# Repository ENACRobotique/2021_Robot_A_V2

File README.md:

# 2021_Robot_A_V2
Code source robot 2A 2021

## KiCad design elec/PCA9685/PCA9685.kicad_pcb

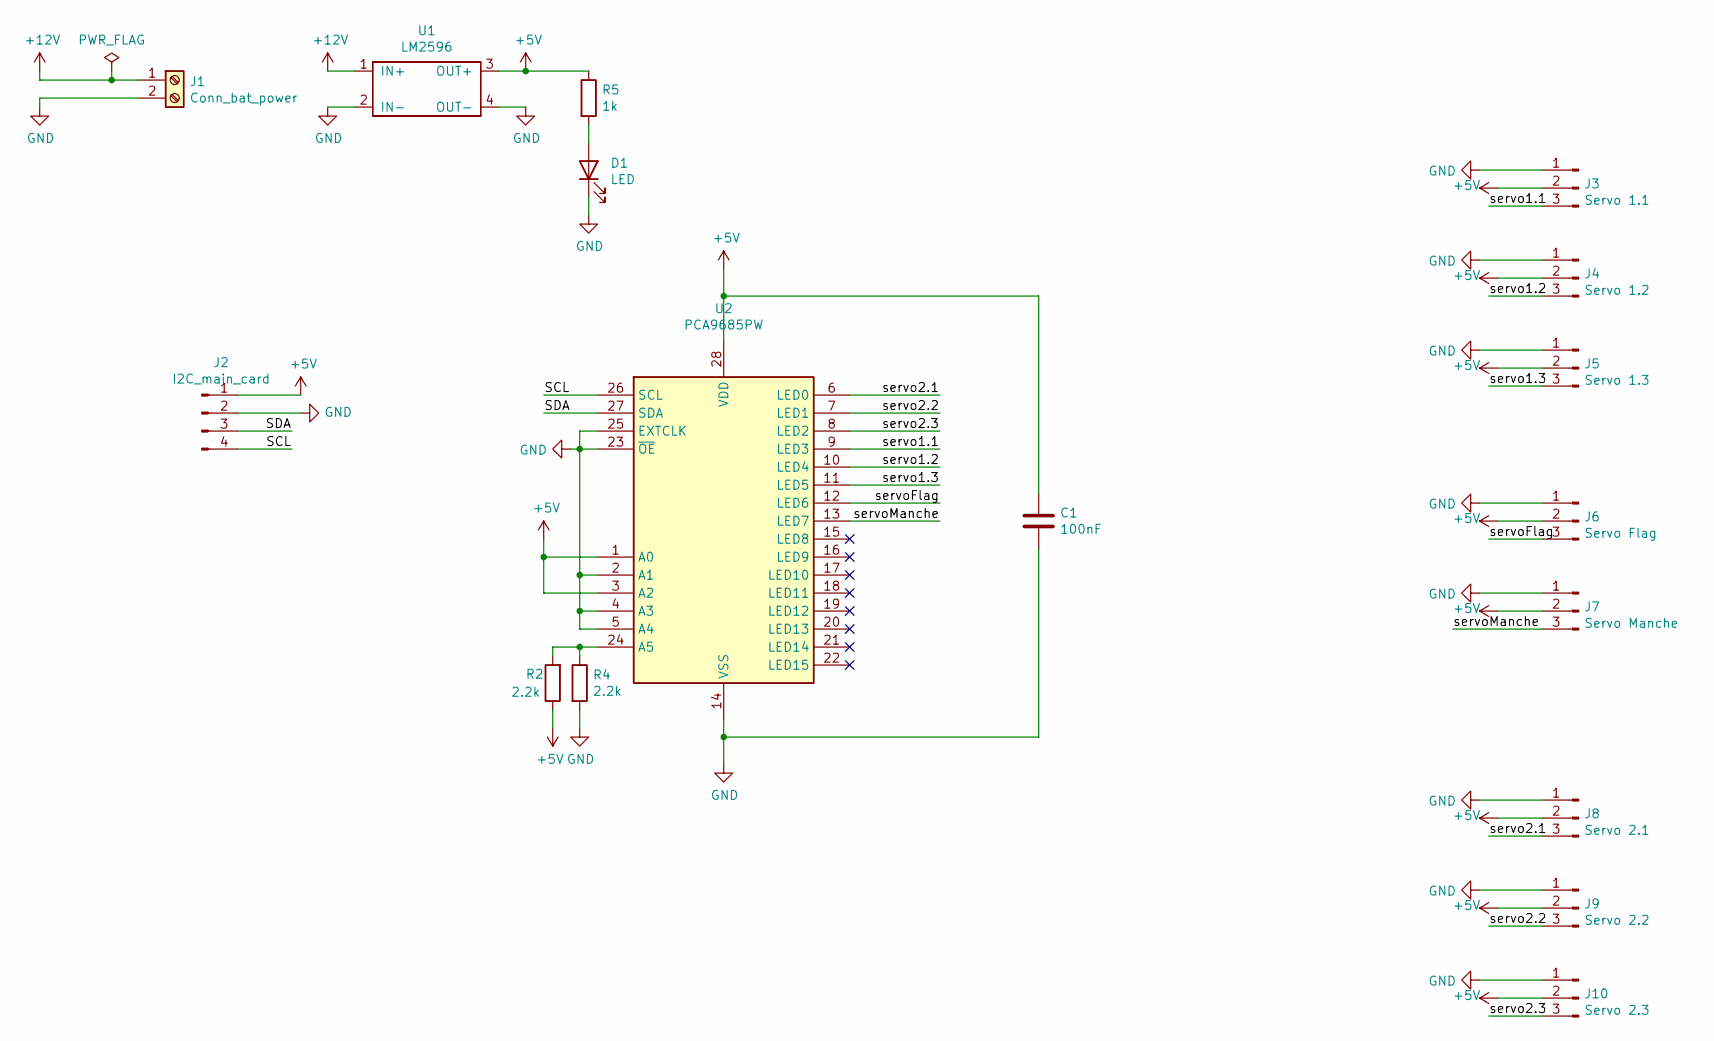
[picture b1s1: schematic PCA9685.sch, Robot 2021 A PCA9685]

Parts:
C1: 100nF; C_0805_2012Metric_Pad1.15x1.40mm_HandSolder
D1: LED; LED_0603_1608Metric_Pad1.05x0.95mm_HandSolder
J1: Conn_bat_power; TerminalBlock_bornier-2_P5.08mm
J2: I2C_main_card; JST_XH_B4B-XH-A_1x04_P2.50mm_Vertical
J3: Servo 1.1; PinHeader_1x03_P2.54mm_Vertical
J4: Servo 1.2; PinHeader_1x03_P2.54mm_Vertical
J5: Servo 1.3; PinHeader_1x03_P2.54mm_Vertical
J6: Servo Flag; PinHeader_1x03_P2.54mm_Vertical
J7: Servo Manche; PinHeader_1x03_P2.54mm_Vertical
J8: Servo 2.1; PinHeader_1x03_P2.54mm_Vertical
J9: Servo 2.2; PinHeader_1x03_P2.54mm_Vertical
J10: Servo 2.3; PinHeader_1x03_P2.54mm_Vertical
R2, R4: 2.2k; R_0805_2012Metric_Pad1.15x1.40mm_HandSolder
R5: 1k; R_0805_2012Metric_Pad1.15x1.40mm_HandSolder
U1: LM2596
U2: PCA9685PW; TSSOP-28_4.4x9.7mm_P0.65mm

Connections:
+5V: C1.1, J2.1, J3.2, J4.2, J5.2, J6.2, J7.2, J8.2, J9.2, J10.2, R2.1, R5.1, U1.3 (OUT+), U2.1 (A0), U2.3 (A2), U2.28 (VDD)
+12V: J1.1, U1.1 (IN+)
/SCL: J2.4, U2.26 (SCL)
/SDA: J2.3, U2.27 (SDA)
/servo1.1: J3.3, U2.9 (LED3)
/servo1.2: J4.3, U2.10 (LED4)
/servo1.3: J5.3, U2.11 (LED5)
/servo2.1: J8.3, U2.6 (LED0)
/servo2.2: J9.3, U2.7 (LED1)
/servo2.3: J10.3, U2.8 (LED2)
/servoFlag: J6.3, U2.12 (LED6)
/servoManche: J7.3, U2.13 (LED7)
GND: C1.2, D1.1 (K), J1.2, J2.2, J3.1, J4.1, J5.1, J6.1, J7.1, J8.1, J9.1, J10.1, R4.2, U1.2 (IN-), U1.4 (OUT-), U2.2 (A1), U2.4 (A3), U2.5 (A4), U2.14 (VSS), U2.23 (~OE), U2.25 (EXTCLK)
unnamed: D1.2 (A), R5.2
unnamed: R2.2, R4.1, U2.24 (A5)

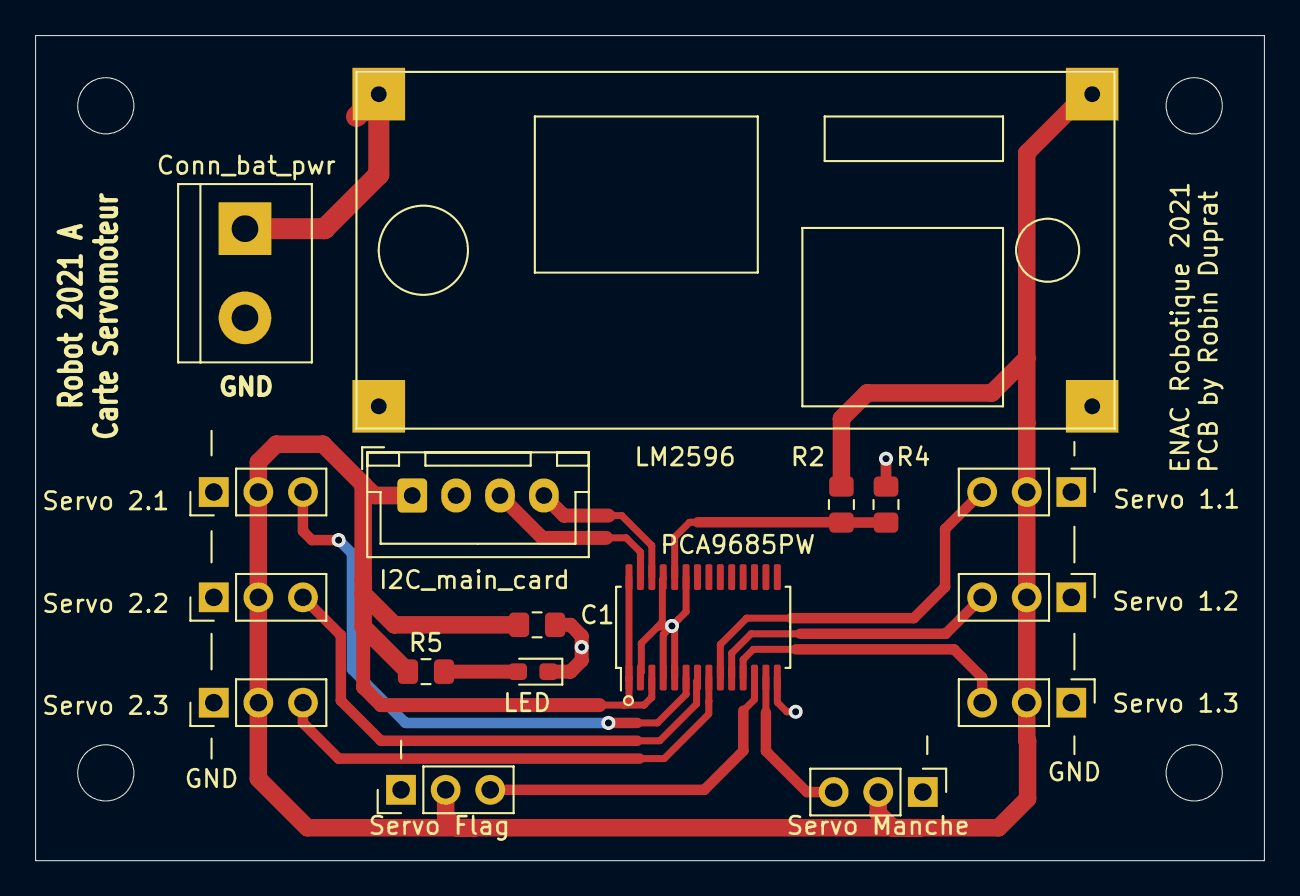
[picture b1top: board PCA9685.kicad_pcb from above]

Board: 2 copper layers, 70.0 x 47.0 mm, 17 parts (0 on the bottom side), 15 nets.

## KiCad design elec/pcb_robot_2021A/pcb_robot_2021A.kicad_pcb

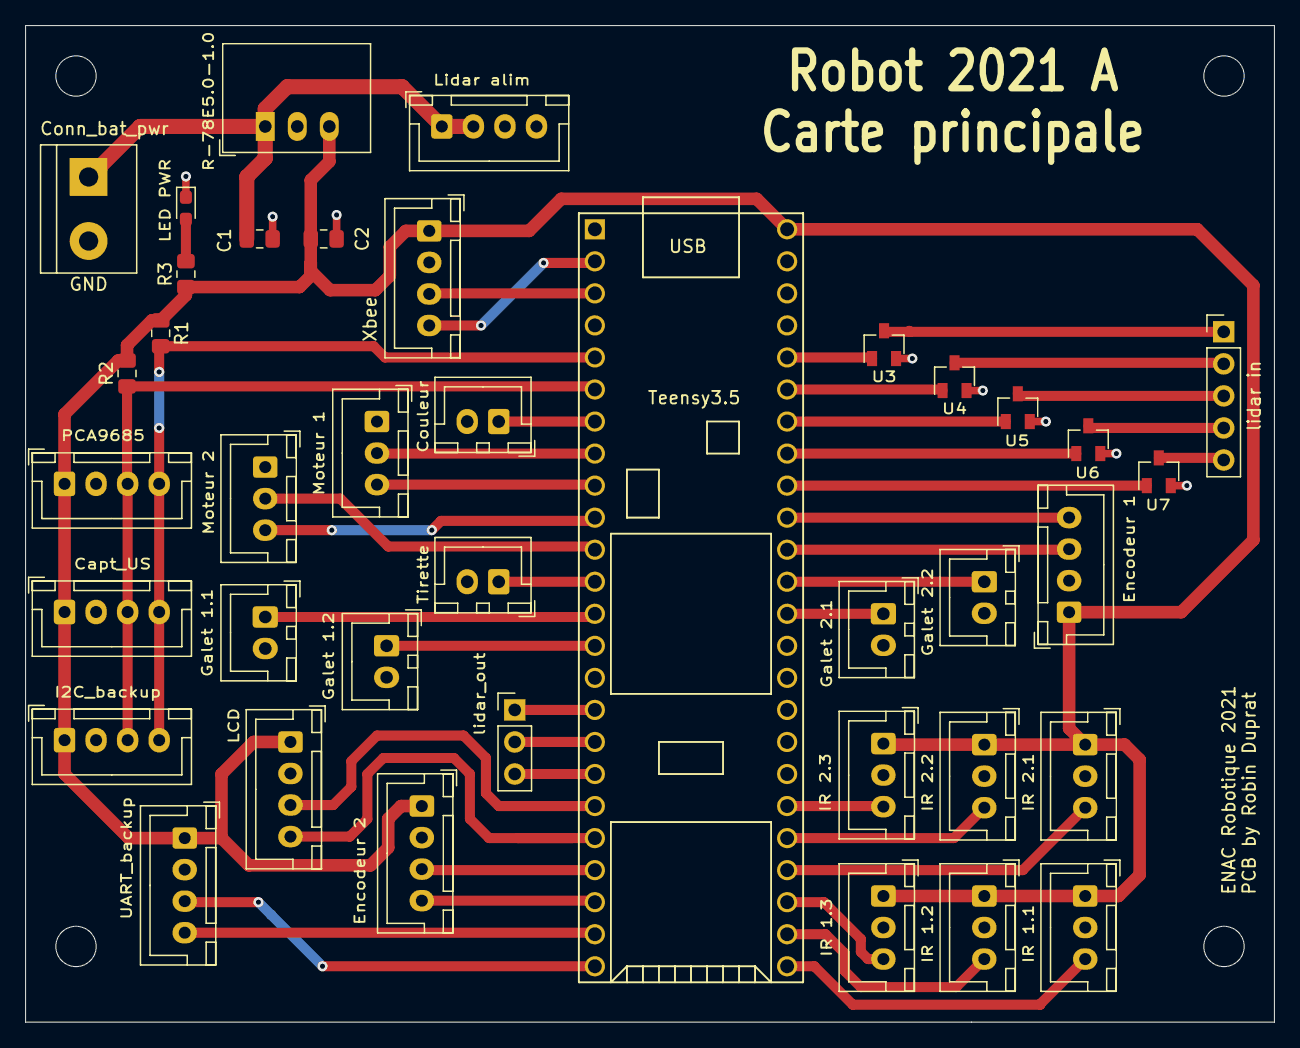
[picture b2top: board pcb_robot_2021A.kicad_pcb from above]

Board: 2 copper layers, 99.0 x 79.0 mm, 39 parts (0 on the bottom side), 45 nets.

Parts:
C1, C2: 10µF; C_0805_2012Metric_Pad1.15x1.40mm_HandSolder
D1: LED PWR; LED_0603_1608Metric_Pad1.05x0.95mm_HandSolder
J1: LCD; JST_XH_B4B-XH-A_1x04_P2.50mm_Vertical
J2: IR 1.1; JST_XH_B3B-XH-A_1x03_P2.50mm_Vertical
J3: IR 1.2; JST_XH_B3B-XH-A_1x03_P2.50mm_Vertical
J4: IR 1.3; JST_XH_B3B-XH-A_1x03_P2.50mm_Vertical
J5: IR 2.1; JST_XH_B3B-XH-A_1x03_P2.50mm_Vertical
J6: IR 2.2; JST_XH_B3B-XH-A_1x03_P2.50mm_Vertical
J7: IR 2.3; JST_XH_B3B-XH-A_1x03_P2.50mm_Vertical
J8: Moteur 1; JST_XH_B3B-XH-A_1x03_P2.50mm_Vertical
J9: Moteur 2; JST_XH_B3B-XH-A_1x03_P2.50mm_Vertical
J10: Encodeur 1; JST_XH_B4B-XH-A_1x04_P2.50mm_Vertical
J11: Encodeur 2; JST_XH_B4B-XH-A_1x04_P2.50mm_Vertical
J12: Conn_bat_pwr; TerminalBlock_bornier-2_P5.08mm
J13: Tirette; JST_XH_B2B-XH-A_1x02_P2.50mm_Vertical
J14: Couleur; JST_XH_B2B-XH-A_1x02_P2.50mm_Vertical
J15: UART_backup; JST_XH_B4B-XH-A_1x04_P2.50mm_Vertical
J16: Xbee; JST_XH_B4B-XH-A_1x04_P2.50mm_Vertical
J17: PCA9685; JST_XH_B4B-XH-A_1x04_P2.50mm_Vertical
J18: Capt_US; JST_XH_B4B-XH-A_1x04_P2.50mm_Vertical
J19: I2C_backup; JST_XH_B4B-XH-A_1x04_P2.50mm_Vertical
J20: lidar in; PinHeader_1x05_P2.54mm_Vertical
J21: lidar_out; PinHeader_1x03_P2.54mm_Vertical
J22: Lidar alim; JST_XH_B4B-XH-A_1x04_P2.50mm_Vertical
J23: Galet 1.1; JST_XH_B2B-XH-A_1x02_P2.50mm_Vertical
J24: Galet 1.2; JST_XH_B2B-XH-A_1x02_P2.50mm_Vertical
J25: Galet 2.1; JST_XH_B2B-XH-A_1x02_P2.50mm_Vertical
J26: Galet 2.2; JST_XH_B2B-XH-A_1x02_P2.50mm_Vertical
R1, R2: 2.2k; R_0805_2012Metric_Pad1.15x1.40mm_HandSolder
R3: 1k; R_0805_2012Metric_Pad1.15x1.40mm_HandSolder
U1: R-78E5.0-1.0; Converter_DCDC_RECOM_R-78E-0.5_THT
U2: Teensy3.5; Teensy35_36
U3: mosfet_lid_I1; SOT-23
U4: mosfet_lid_I2; SOT-23
U5: mosfet_lid_I3; SOT-23
U6: mosfet_lid_I4; SOT-23
U7: mosfet_lid_I5; SOT-23

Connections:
+5V: C2.1, J1.1, J2.1, J3.1, J4.1, J5.1, J6.1, J7.1, J10.1, J11.1, J15.1, J16.1, J17.1, J18.1, J19.1, R1.1, R2.2, R3.1, U1.3, U2.53
+12V: C1.1, J12.1, J22.1, J22.2, U1.1
/IR_out1.1: J2.3, U2.30
/IR_out1.2: J3.3, U2.31
/IR_out1.3: J4.3, U2.32
/IR_out2.1: J5.3, U2.33
/IR_out2.2: J6.3, U2.34
/IR_out2.3: J7.3, U2.35
/LCD_1: J1.3, U2.19
/LCD_2: J1.4, U2.20
/RX4: J15.4, U2.23
/SCL: J17.4, J18.4, J19.4, R1.2, U2.5
/SDA: J17.3, J18.3, J19.3, R2.1, U2.6
/TX4: J15.3, U2.24
/Xbee_RX: J16.4, U2.2
/Xbee_TX: J16.3, U2.3
/couleur: J14.1, U2.7
/enc1_A: J10.3, U2.43
/enc1_B: J10.4, U2.44
/enc2_A: J11.3, U2.21
/enc2_B: J11.4, U2.22
/galet_1.1: J23.1, U2.13
/galet_1.2: J24.1, U2.14
/galet_2.1: J25.1, U2.41
/galet_2.2: J26.1, U2.42
/lidar_in1: U2.49, U3.1
/lidar_in2: U2.48, U4.1
/lidar_in3: U2.47, U5.1
/lidar_in4: U2.46, U6.1
/lidar_in5: U2.45, U7.1
/lidar_out1: J21.1, U2.16
/lidar_out2: J21.2, U2.17
/lidar_out3: J21.3, U2.18
/mot1_PWM: J8.2, U2.8
/mot1_dir: J8.3, U2.9
/mot2_PWM: J9.2, U2.11
/mot2_dir: J9.3, U2.10
/tirette: J13.1, U2.12
GND: C1.2, C2.2, D1.1, J1.2, J2.2, J3.2, J4.2, J5.2, J6.2, J7.2, J8.1, J9.1, J10.2, J11.2, J12.2, J13.2, J14.2, J15.2, J16.2, J17.2, J18.2, J19.2, J22.3, J22.4, J23.2, J24.2, J25.2, J26.2, U1.2, U2.1, U3.2, U4.2, U5.2, U6.2, U7.2
unnamed: D1.2, R3.2
unnamed: J20.1, U3.3
unnamed: J20.2, U4.3
unnamed: J20.3, U5.3
unnamed: J20.4, U6.3
unnamed: J20.5, U7.3

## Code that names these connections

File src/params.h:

/*
 * params.h
 *
 *  Created on: 18 mars 2018
 *      Author: elie
 */

#ifndef PARAMS_H_
#define PARAMS_H_
#include "Arduino.h"

#define VOLT_TO_DIST(volt) (5.079395 * pow (volt, -1.186)) 

const int ARUCO_ID = 5;

const unsigned long TIME_RACE = 100000;


const int ENCODEUR1_A = 16;
const int ENCODEUR1_B = 17;
const int ENCODEUR2_A = 29;
const int ENCODEUR2_B = 30;

const int MOT1_PWM = 6;
const int MOT1_DIR = 7;
const int MOT2_PWM = 9;
const int MOT2_DIR = 8;

//const int BATT_CHARGE = 37;

// const int US_RANGE = 35;
// const int US_RANGE_DIMINUSHED = 25;

// const int SERVO1 = 39;
// const int SERVO2 = 15;
const int SERVO3 = 37;

// const int MOT_GALET_L = 35;
// const int MOT_LIDAR = 35;

const int COLOR = 5;
const int TIRETTE = 10; //old 25

const int LIDARIN1 = 18;
const int LIDARIN2 = 19;
const int LIDARIN3 = 20;
const int LIDARIN4 = 21;
const int LIDARIN5 = 22;

const int LIDAROUT1 = 24;
const int LIDAROUT2 = 25;
const int LIDAROUT3 = 26;

// const int SPARE1 = 10;
// const int SPARE2 = 9;
// const int SPARE3 = 8;
// const int SPARE4 = 7;

// const int DYNAMIXEL_CONTROL = 30;
// const int DYNAMIXEL_ID =1;

const int EMERGENCY_BRAKE = 1800;
const int ACCEL_MAX = 500;
const int ACCEL_MAX_THROW = 100;
const int SPEED_MAX_CRUISE = 350;

const int ACCEL_MAX_CAP = 100;
const int SPEED_MAX_CAP = 100;

const float ACCEL_OMEGA_MAX_CRUISE = 1;
const float OMEGA_MAX_CRUISE = 1.5;

const float ACCEL_OMEGA_MAX_CAP = 0.3;
const float OMEGA_MAX_CAP = 0.5;

const float ADMITTED_ANGLE_ERROR_CRUISE = 70*PI/180;

const float ADMITTED_OMEGA_ERROR = 0.03;
const float ADMITTED_SPEED_ERROR = 10;

const float ADMITTED_POSITION_ERROR = 8; //5
const float ADMITTED_ANGLE_ERROR = 0.01;

//const float MAX_DRIFT = 0.1;

//const float WHEEL_DIAMETER = 55.0;
const float WHEELBASE = 227.28;//261.9790233;
const float INCR_TO_MM = 0.21922110552763818;   //PI*WHEEL_DIAMETER/805.12;
const float INCR_TO_MM_1 = INCR_TO_MM * 0.9833721540716956;
const float INCR_TO_MM_2 = INCR_TO_MM * 1.016909006279521;
//const float INCR_TO_TOURS = 1/805.12;
const float CONTROL_PERIOD = 0.02;
const float NAVIGATOR_PERIOD = 0.05;
const float COMMUNICATION_PERIOD = 0.1;
const float STATE_PERIOD = 0.1;

const unsigned long THROW_DURATION = 20000;
const unsigned long SERVO_MOVEMENT_DURATION = 1000;
const unsigned long DETECTION_STOP_TIME = 1500;

const int GREEN = 1;
const int ORANGE = !GREEN;
const int PURPLE = 1;
const int YELLOW = !PURPLE;


enum sensors {IR_FL=33,IR_FC,IR_FR,IR_BL,IR_BC,IR_BR,IR_test};

enum servos {
    servo_FL,   //2.1
    servo_FC,   //2.2
    servo_FR,   //2.3
    servo_BL,   //1.1
    servo_BC,   //1.2
    servo_BR,   //1.3
    };


//params de capture ecocup
const float dist_min=5,dist_max=25;//valeurs initial turn
const float delta_step_forward=20;// marge sur la trajecture de capture en mm
const float nominal_delta_rot=30;//degres
const float dist_opt=4.5;
const float rayon_eco=3.1; //4.0 //3.1 //rayon mesuré écocup en cm
const float L_anneaux=75; //distance entre deux anneaux en mm



//params servos

const uint16_t init_tab[8] = {
    180,  // 2.1
    180,  // 2.2
    180,  // 2.3
    180,  // 1.1
    180,  // 1.2
    180,  // 1.3
    180,  // flag
    180   // manche
};
// const int NB_US = 4;

//paramètres de chemin, algorithme A*, noeuds, concurrents/adversaires, segments/arêtes 
// voir aetoile/grilnav.hpp
#endif /* PARAMS_H_ */

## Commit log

2021-02-11 Commit initial
2021-02-11 Ajout stateMachine
2021-02-11 Ajout stateMachine v2
2021-02-11 Supression anciens fichiers
2021-02-11 Ajout raspberryParser
2021-02-11 inclusion raspberryParser dans communication.cpp
2021-02-13 servo test and library controlServo
2021-02-13 Ajout test servo
2021-02-13 début kalman
2021-02-16 Initialisation elec
2021-02-19 qques lignes en + pour kalman
2021-02-20 Ajout moteur, tirette, couleur, début lidar et interrupteur galet
2021-02-20 update lidar
2021-02-21 Connectique lidar hokuyo
2021-02-21 add PCA9685 conn on main card
2021-02-21 update conn on teensy
2021-02-21 schematic for PCA9685 (conn 8 servos)
2021-02-21 fin v1 PCA et main carte
2021-02-25 fin sch carte principale
2021-03-01 positionnement item sur le pcb de main card
2021-03-01 Fin première version routage main card
2021-03-01 empreintes carte PAC9685
2021-03-01 modif capture + reajustement only
2021-03-01 commit reajustement + capture v2
2021-03-02 Routage carte PCA9685
2021-03-03 ajout commande vitesse (via navigator) et communication
2021-03-03 version test capteur
2021-03-03 correction state reajustement et ajout etat test
2021-03-03 Carte Principale V2 : Plus petite, correction de position de via et de connecteurs, bande plus large, ajout des trous de fixation
2021-03-03 Carte PCA9695 V2 : piste plus large, meilleur routage, texte au bon endroit et ajout des trous Carte Principale : Patch du texte, récupération d'une dizaine de mm sur un côté
2021-03-03 Carte Principale : 99mm de long !!!
2021-03-04 L'alignement des trous, c'est important
2021-03-04 Tentative de logo ENAC : echec Mise à jour visuelle, finission des cadres et plan de masse
2021-03-04 Patch footprint connecteurs servo sur carte PAC9685
2021-03-04 Mise à jour espacement connecteur servo sur carte PCA9685
2021-03-04 affinage capture eco cup + ajout dans communication.cpp
2021-03-06 Parser + kalman
2021-03-06 kalman
2021-03-06 test de kalman données théoriques la prochaine fois
2021-03-06 String dans arduino.h, pas string.h
2021-03-09 Final push
2021-03-10 classe klm
2021-03-10 kalman à corriger
2021-03-11 arm_math
2021-03-11 ajout de l'état travel
2021-03-11 ajout classe trajectory
2021-03-11 fgfdg
2021-03-11 ça marhce un peu
2021-03-12 git pas content à cause platformio.ini
2021-03-12 hrefjvdsuiguievg
2021-03-12 hgqjkds
2021-03-12 hfdklj
2021-03-12 kalman/odometrie: vérifier pos init et axes
2021-03-13 revenir en arrière la prochaine fois
2021-03-13 réécriture navigator update
2021-03-13 reparation forceStop
2021-03-14 fqksdhfhs
2021-03-14 switchfix
2021-03-14 modif navigator ergonomie
2021-04-09 correction d'un petit truc
2021-04-14 impl traj + tirette
2021-05-04 ajout du code LIDAR
2021-05-04 en tête .h
2021-05-05 Implementation lidar
2021-05-05 Lidar mais marche pas
2021-05-11 Ajout des library adafruit
2021-05-19 correction lidar
2021-05-21 ajout capture offset position IR latéraux
2021-05-26 integration I2C + update calcul IR
2021-06-02 corrections sur capture
2021-06-03 ajout ecocupmanager, àtester
2021-06-03 retire captureRed inutile
2021-06-04 version qui marche parfois pour attraper deux ecocups rouges et les déposer à l'endroit voulu (ou pas loin)
2021-06-07 traj et tirette - code trouvé le 7 juin
2021-06-14 Mise à jour de Paul
2021-06-25 cleanup trajectory
2021-06-27 merging in progres - not compiling
2021-06-28 debut merge
2021-07-04 ajout d'une gestionnaire de taches, gestion de trajectoires basé sur une grille de navigation : le robot passe obligatoirement par des aretes prédéfinies. recherche de chemin entre deux points par a*
2021-07-04 lien (le vrai) entre parcours et navigation
